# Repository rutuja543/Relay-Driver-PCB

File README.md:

# 🔌 Relay Driver PCB

A relay driver circuit designed using **KiCad** to safely control AC/DC loads from low-power microcontrollers such as **Arduino**, **ESP32**, and **STM32**. The design uses an NPN transistor as a switching device and includes a flyback diode to protect the transistor from relay back EMF.

---

## 📌 Project Overview

This project demonstrates the design of a relay driver PCB that enables microcontrollers to switch high-current electrical loads safely. The PCB is compact, easy to assemble, and suitable for automation and embedded system applications.

---

## 🎯 Objectives

- Design a reliable relay driver PCB
- Interface low-voltage controllers with high-power loads
- Protect switching transistor using a flyback diode
- Learn PCB schematic and layout design using KiCad

---

## ⚙️ Features

- NPN transistor based relay driver
- Flyback diode protection
- LED status indicator
- Screw terminal connectors
- Compact single-layer PCB
- Easy Arduino and ESP32 interfacing
- Noise-resistant routing

---

## 🛠 Software Used

- KiCad 8
- Arduino IDE (for testing)

---

## 🔩 Hardware Components

- Relay Module (5V/12V)
- BC547 / 2N2222 NPN Transistor
- 1N4007 Flyback Diode
- Base Resistor
- LED
- Current Limiting Resistor
- Screw Terminal Connectors
- Power Supply Connector

---

## 🔄 Working Principle

1. The microcontroller sends a HIGH signal.
2. The transistor turns ON.
3. Current flows through the relay coil.
4. The relay energizes and switches the external load.
5. The flyback diode suppresses reverse voltage generated by the relay coil during switching.

---

## 📂 Repository Structure

```
Relay-Driver-PCB
│
├── README.md
├── Relay_Driver.kicad_sch
├── Relay_Driver.kicad_pcb
├── Images/
│   ├── Schematic.png
│   └── PCB_Layout.png
└── Gerber/
```

---

## 📷 Project Images

### Circuit Schematic

(Add screenshot here)

### PCB Layout

(Add screenshot here)

### 3D PCB View

(Add screenshot here)

---

## 🚀 Applications

- Home Automation
- Industrial Automation
- IoT Projects
- Smart Switches
- Embedded Systems
- Motor Control
- Appliance Control

---

## 📚 Skills Demonstrated

- PCB Design
- Schematic Design
- Electronic Circuit Design
- KiCad
- Embedded Hardware Design
- Power Electronics Basics

---

## 📈 Future Improvements

- Optocoupler Isolation
- Multiple Relay Channels
- Fuse Protection
- Terminal Labeling
- PCB Silkscreen Improvements

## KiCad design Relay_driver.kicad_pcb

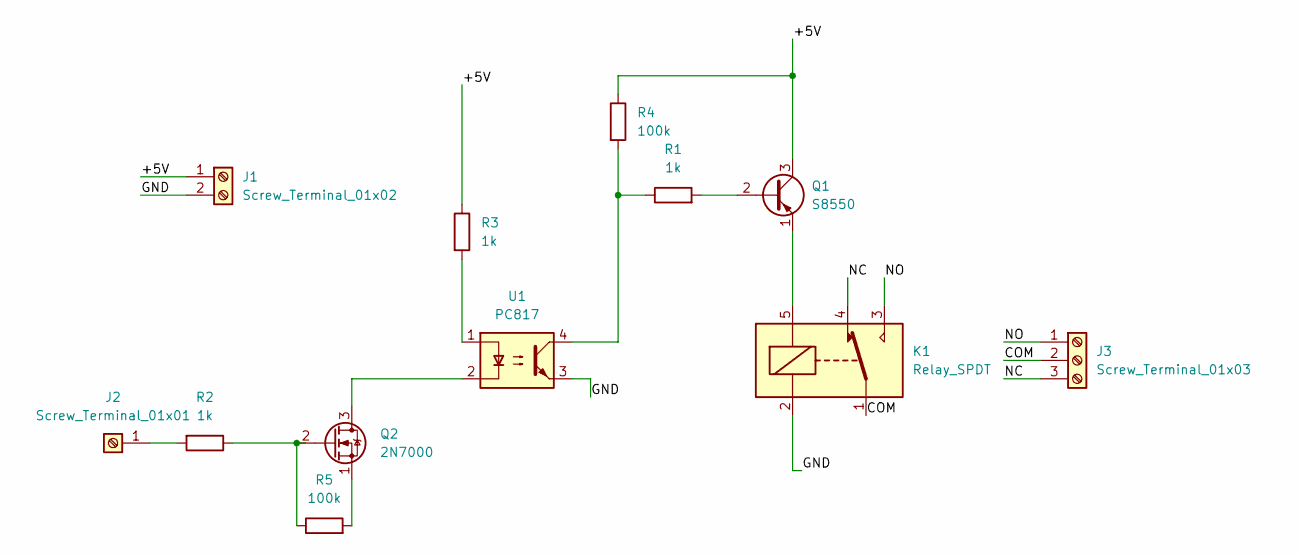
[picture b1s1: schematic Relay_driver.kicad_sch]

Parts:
J1: Screw_Terminal_01x02; TerminalBlock_Phoenix_MKDS-1,5-2-5.08_1x02_P5.08mm_Horizont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
J2: Screw_Terminal_01x01; TerminalBlock_MetzConnect_360271_1x01_Horizontal_ScrewM3.0_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
J3: Screw_Terminal_01x03; TerminalBlock_Phoenix_MKDS-1,5-3-5.08_1x03_P5.08mm_Horizont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
K1: Relay_SPDT; Relay_SPDT_SANYOU_SRD_Series_Form_C
Q1: S8550; TO-92_Inline
Q2: 2N7000; TO-92_Inline
R1, R2, R3: 1k; R_Axial_DIN0204_L3.6mm_D1.6mm_P5.08mm_Horizontal
R4, R5: 100k; R_Axial_DIN0204_L3.6mm_D1.6mm_P5.08mm_Horizontal
U1: PC817; DIP-4_W7.62mm

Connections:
/+5V: J1.1, Q1.3 (C), R3.1, R4.1
/COM: J3.2, K1.1
/GND: J1.2, K1.2, U1.3
/NC: J3.3, K1.4
/NO: J3.1, K1.3
unnamed: J2.1, R2.2
unnamed: Q1.2 (B), R1.2
unnamed: K1.5, Q1.1 (E)
unnamed: Q2.3 (D), U1.2
unnamed: Q2.2 (G), R2.1, R5.1
unnamed: Q2.1 (S), R5.2
unnamed: R1.1, R4.2, U1.4
unnamed: R3.2, U1.1

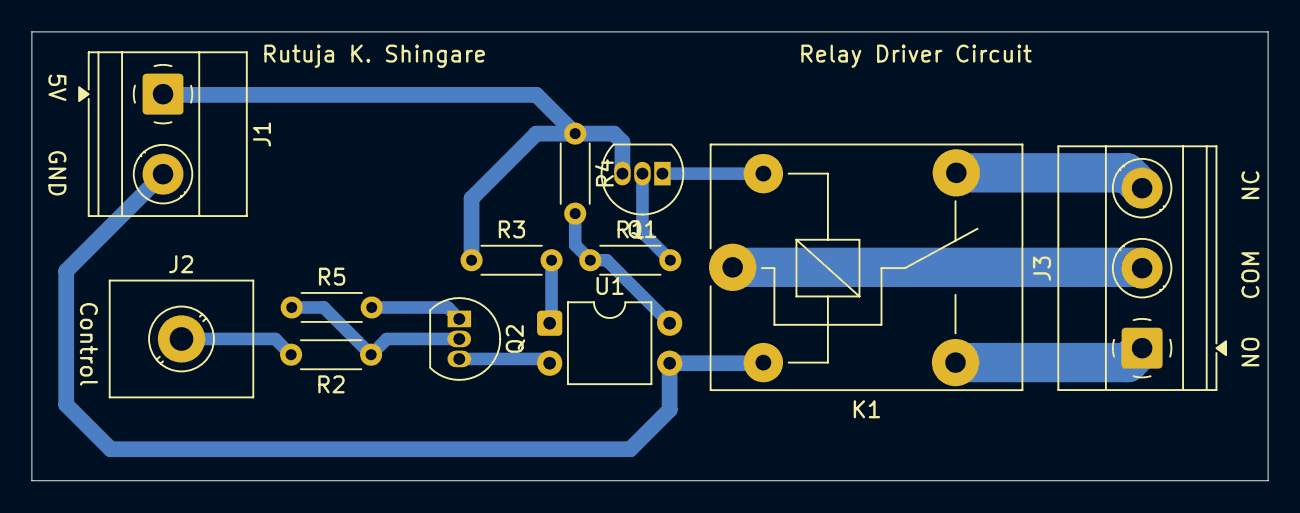
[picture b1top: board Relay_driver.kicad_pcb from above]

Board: 2 copper layers, 78.5 x 28.5 mm, 12 parts (0 on the bottom side), 13 nets.
